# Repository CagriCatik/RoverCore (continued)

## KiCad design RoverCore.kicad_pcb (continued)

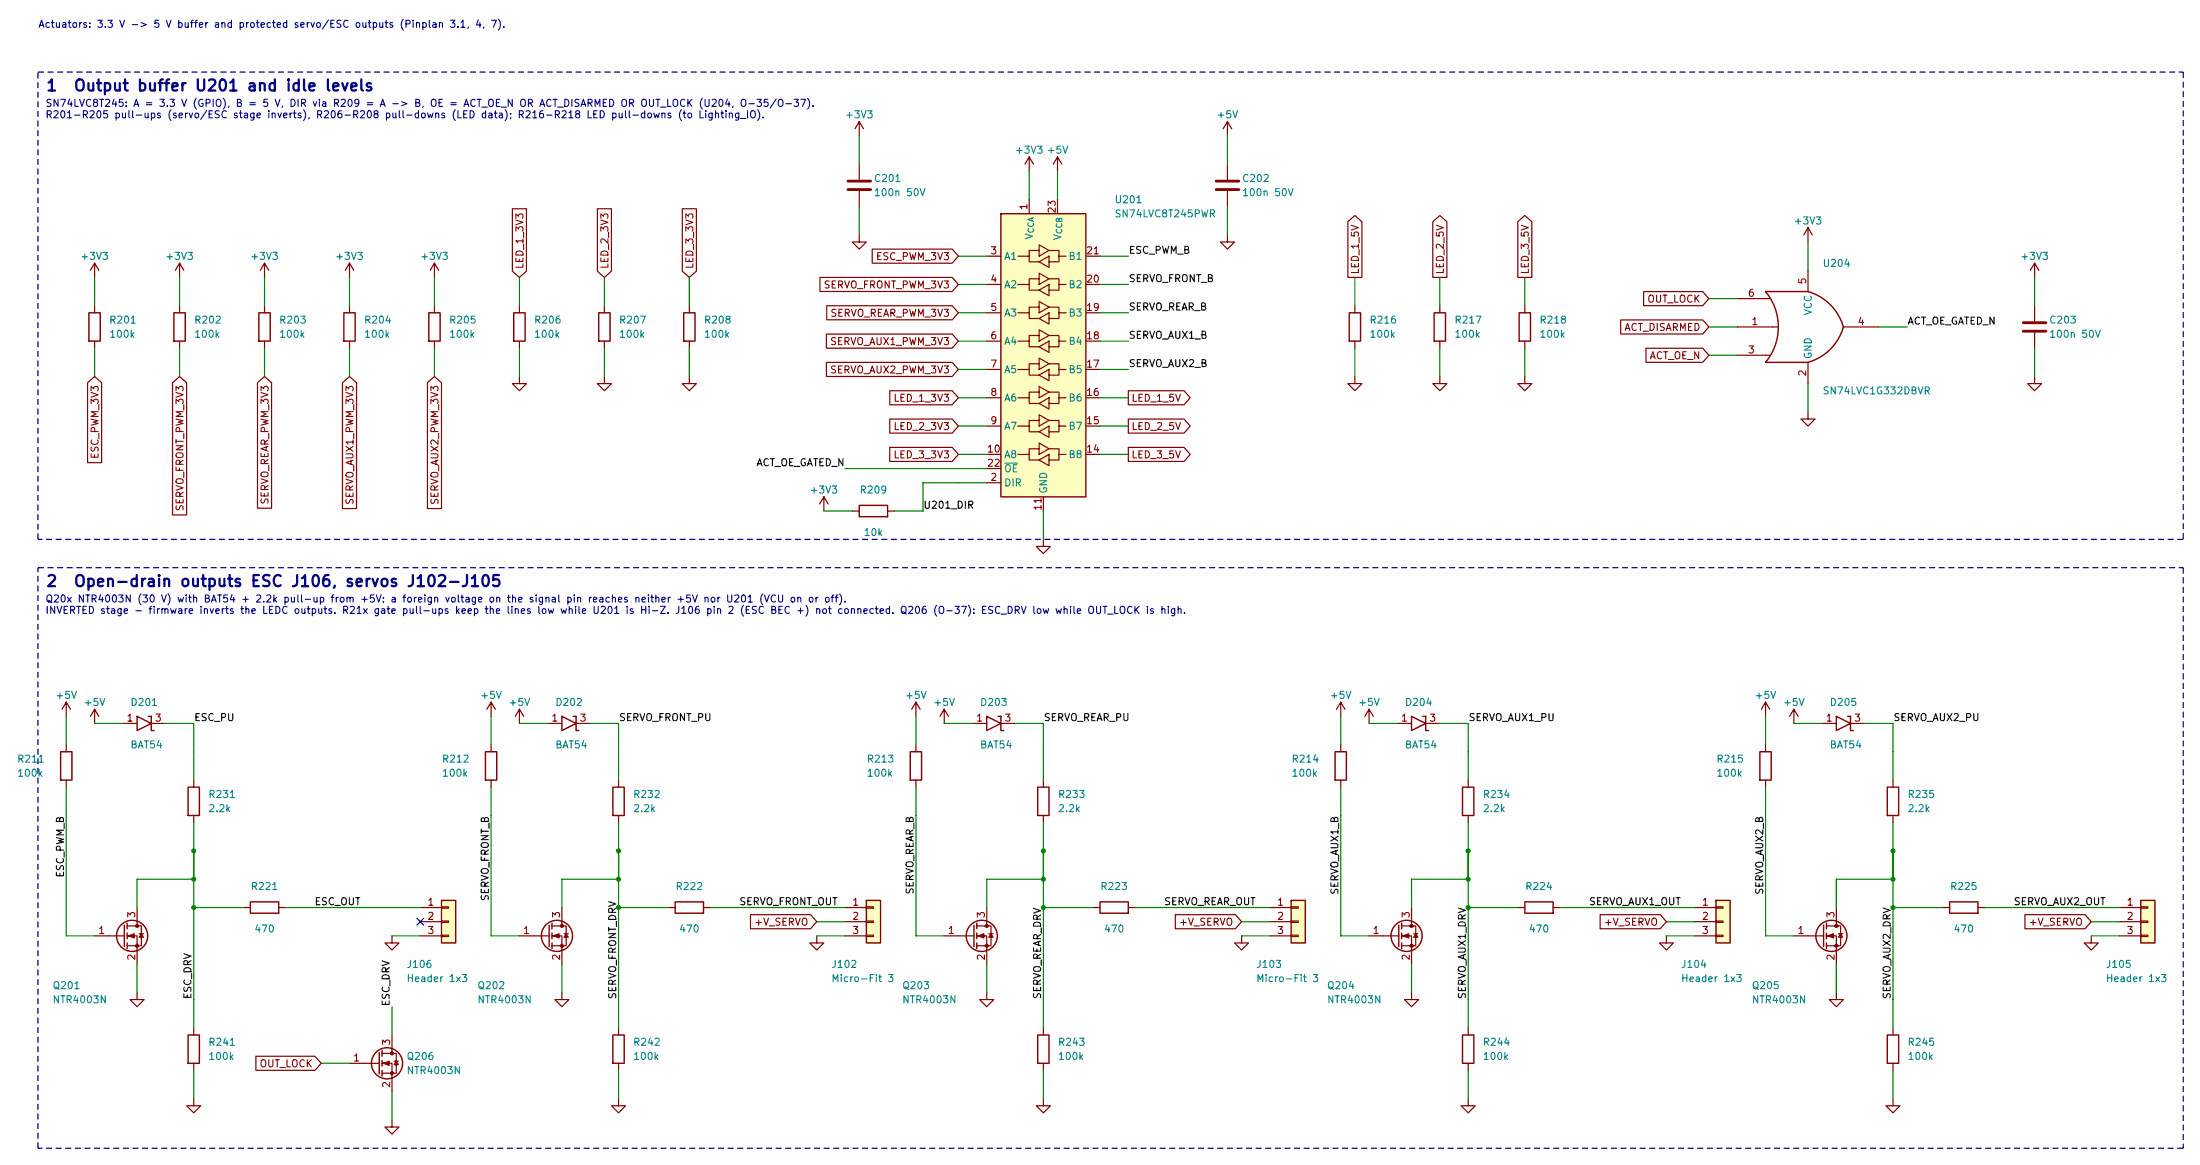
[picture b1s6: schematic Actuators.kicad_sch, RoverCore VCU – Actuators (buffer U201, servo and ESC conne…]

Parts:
C201, C202, C203: 100n 50V; C_0603_1608Metric; MPN CC0603KRX7R9BB104; LCSC C14663
D201, D202, D203, D204, D205: BAT54; SOT-23; MPN BAT54,215; LCSC C85084
J102, J103: Micro-Fit 3; Molex_Micro-Fit_3.0_43650-0300_1x03_P3.00mm_Horizontal; MPN 43650-0300; LCSC C503478
J104, J105, J106: Header 1x3; PinHeader_1x03_P2.54mm_Vertical; MPN 1x3 pin header 2.54 mm, vertical (part 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
Q201, Q202, Q203, Q204, Q205, Q206: NTR4003N; SOT-23; MPN NTR4003NT1G; LCSC C82325
R201, R202, R203, R204, R205, R206, R207, R208, R211, R212, R213, R214, R215, R216, R217, R218, R241, R242, R243, R244, R245: 100k; R_0603_1608Metric; MPN RC0603FR-07100KL; LCSC C14675
R209: 10k; R_0603_1608Metric; MPN RC0603FR-0710KL; LCSC C98220
R221, R222, R223, R224, R225: 470; R_0603_1608Metric; MPN RC0603FR-07470RL; LCSC C114669
R231, R232, R233, R234, R235: 2.2k; R_0603_1608Metric; MPN RC0603FR-072K2L; LCSC C114662
U201: SN74LVC8T245PWR; TSSOP-24_4.4x7.8mm_P0.65mm; MPN SN74LVC8T245PWR; LCSC C27643
U204: SN74LVC1G332DBVR; SOT-23-6; MPN SN74LVC1G332DBVR; LCSC C43368

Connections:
+3V3: C201.1, C203.1, R201.1, R202.1, R203.1, R204.1, R205.1, R209.1, U201.1 (V_{CCA}), U204.5 (VCC); also elsewhere on the board
+5V: C202.1, D201.1 (A), D202.1 (A), D203.1 (A), D204.1 (A), D205.1 (A), R211.1, R212.1, R213.1, R214.1, R215.1, U201.23 (V_{CCB}), U201.24 (V_{CCB}); also elsewhere on the board
+V_SERVO: J102.2, J103.2, J104.2, J105.2; also elsewhere on the board
/Actuators/ACT_OE_GATED_N: U201.22 (~OE), U204.4
/Actuators/ESC_DRV: Q201.3 (D), Q206.3 (D), R221.1, R231.2, R241.1
/Actuators/ESC_OUT: J106.1, R221.2
/Actuators/ESC_PU: D201.3 (K), R231.1
/Actuators/ESC_PWM_B: Q201.1 (G), R211.2, U201.21 (B1)
/Actuators/SERVO_AUX1_B: Q204.1 (G), R214.2, U201.18 (B4)
/Actuators/SERVO_AUX1_DRV: Q204.3 (D), R224.1, R234.2, R244.1
/Actuators/SERVO_AUX1_OUT: J104.1, R224.2
/Actuators/SERVO_AUX1_PU: D204.3 (K), R234.1
/Actuators/SERVO_AUX2_B: Q205.1 (G), R215.2, U201.17 (B5)
/Actuators/SERVO_AUX2_DRV: Q205.3 (D), R225.1, R235.2, R245.1
/Actuators/SERVO_AUX2_OUT: J105.1, R225.2
/Actuators/SERVO_AUX2_PU: D205.3 (K), R235.1
/Actuators/SERVO_FRONT_B: Q202.1 (G), R212.2, U201.20 (B2)
/Actuators/SERVO_FRONT_DRV: Q202.3 (D), R222.1, R232.2, R242.1
/Actuators/SERVO_FRONT_OUT: J102.1, R222.2
/Actuators/SERVO_FRONT_PU: D202.3 (K), R232.1
/Actuators/SERVO_REAR_B: Q203.1 (G), R213.2, U201.19 (B3)
/Actuators/SERVO_REAR_DRV: Q203.3 (D), R223.1, R233.2, R243.1
/Actuators/SERVO_REAR_OUT: J103.1, R223.2
/Actuators/SERVO_REAR_PU: D203.3 (K), R233.1
/Actuators/U201_DIR: R209.2, U201.2 (DIR)
ACT_DISARMED: U204.1; also elsewhere on the board
ACT_OE_N: U204.3; also elsewhere on the board
ESC_PWM_3V3: R201.2, U201.3 (A1); also elsewhere on the board
GND: C201.2, C202.2, C203.2, J102.3, J103.3, J104.3, J105.3, J106.3, Q201.2 (S), Q202.2 (S), Q203.2 (S), Q204.2 (S), Q205.2 (S), Q206.2 (S), R206.2, R207.2, R208.2, R216.2, R217.2, R218.2, R241.2, R242.2, R243.2, R244.2, R245.2, U201.11 (GND), U201.12 (GND), U201.13 (GND), U204.2 (GND); also elsewhere on the board
LED_1_3V3: R206.1, U201.8 (A6); also elsewhere on the board
LED_1_5V: R216.1, U201.16 (B6); also elsewhere on the board
LED_2_3V3: R207.1, U201.9 (A7); also elsewhere on the board
LED_2_5V: R217.1, U201.15 (B7); also elsewhere on the board
LED_3_3V3: R208.1, U201.10 (A8); also elsewhere on the board
LED_3_5V: R218.1, U201.14 (B8); also elsewhere on the board
OUT_LOCK: Q206.1 (G), U204.6; also elsewhere on the board
SERVO_AUX1_PWM_3V3: R204.2, U201.6 (A4); also elsewhere on the board
SERVO_AUX2_PWM_3V3: R205.2, U201.7 (A5); also elsewhere on the board
SERVO_FRONT_PWM_3V3: R202.2, U201.4 (A2); also elsewhere on the board
SERVO_REAR_PWM_3V3: R203.2, U201.5 (A3); also elsewhere on the board

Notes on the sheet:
1 Output buffer U201 and idle levels
SN74LVC8T245: A = 3.3 V (GPIO), B = 5 V, DIR via R209 = A -> B, OE = ACT_OE_N OR ACT_DISARMED OR OUT_LOCK (U204, O-35/O-37). R201-R205 pull-ups (servo/ESC stage inverts), R206-R208 pull-downs (LED data); R216-R218 LED pull-downs (to Lighting_IO).
2 Open-drain outputs ESC J106, servos J102-J105
Q20x NTR4003N (30 V) with BAT54 + 2.2k pull-up from +5V: a foreign voltage on the signal pin reaches neither +5V nor U201 (VCU on or off). INVERTED stage - firmware inverts the LEDC outputs. R21x gate pull-ups keep the lines low while U201 is Hi-Z. J106 pin 2 (ESC BEC +) not connected. Q206 (O-37):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
Actuators: 3.3 V -> 5 V buffer and protected servo/ESC outputs (Pinplan 3.1, 4, 7).

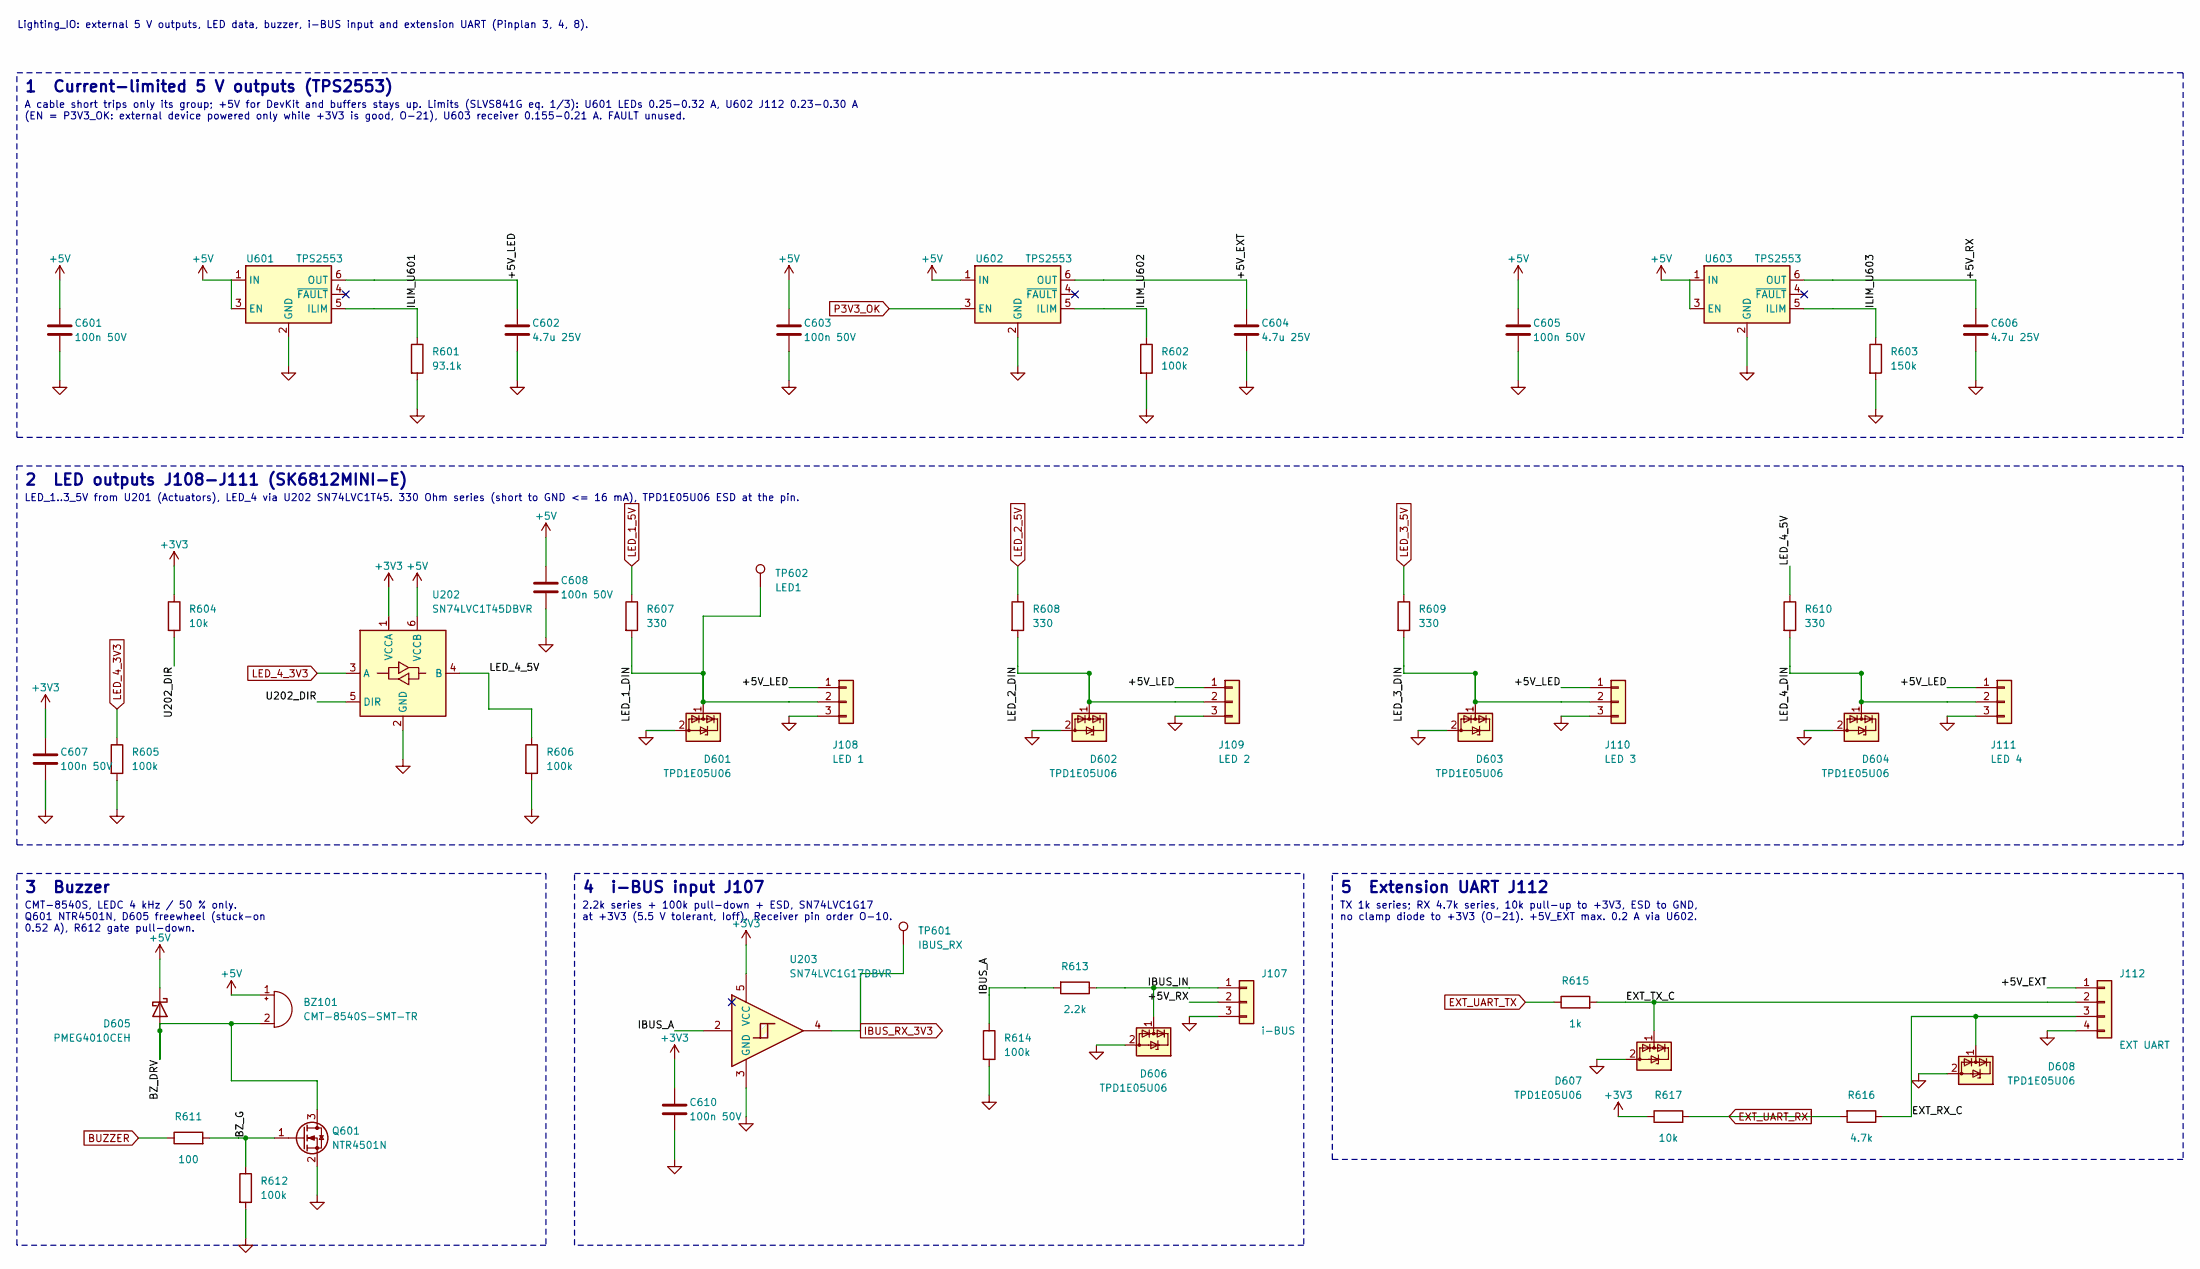
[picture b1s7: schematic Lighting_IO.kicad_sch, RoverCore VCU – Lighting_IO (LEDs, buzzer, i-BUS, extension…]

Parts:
BZ101: CMT-8540S-SMT-TR; MagneticBuzzer_SameSky_CMT-8540S-SMT; MPN CMT-8540S-SMT-TR; LCSC open (LCSC stock 0, O-23)
C601, C603, C605, C607, C608, C610: 100n 50V; C_0603_1608Metric; MPN CC0603KRX7R9BB104; LCSC C14663
C602, C604, C606: 4.7u 25V; C_0805_2012Metric; MPN CC0805KKX7R8BB475; LCSC C354262
D601, D602, D603, D604, D606, D607, D608: TPD1E05U06; Texas_DPY0002A_0.6x1mm_P0.65mm; MPN TPD1E05U06DPYR; LCSC C436349
D605: PMEG4010CEH; D_SOD-123F; MPN PMEG4010CEH,115; LCSC C193342
J107: i-BUS; PinHeader_1x03_P2.54mm_Vertical; MPN 1x3 pin header 2.54 mm (part open)
J108: LED 1; JST_PH_B3B-PH-K_1x03_P2.00mm_Vertical; MPN B3B-PH-K-S(LF)(SN); LCSC open (O-22)
J109: LED 2; JST_PH_B3B-PH-K_1x03_P2.00mm_Vertical; MPN B3B-PH-K-S(LF)(SN); LCSC open (O-22)
J110: LED 3; JST_PH_B3B-PH-K_1x03_P2.00mm_Vertical; MPN B3B-PH-K-S(LF)(SN); LCSC open (O-22)
J111: LED 4; JST_PH_B3B-PH-K_1x03_P2.00mm_Vertical; MPN B3B-PH-K-S(LF)(SN); LCSC open (O-22)
J112: EXT UART; JST_PH_B4B-PH-K_1x04_P2.00mm_Vertical; MPN B4B-PH-K-S(LF)(SN); LCSC open (O-22)
Q601: NTR4501N; SOT-23; MPN NTR4501NT1G; LCSC C85416
R601: 93.1k; R_0603_1608Metric; MPN RC0603FR-0793K1L; LCSC C273780
R602, R605, R606, R612, R614: 100k; R_0603_1608Metric; MPN RC0603FR-07100KL; LCSC C14675
R603: 150k; R_0603_1608Metric; MPN RC0603FR-07150KL; LCSC C114660
R604, R617: 10k; R_0603_1608Metric; MPN RC0603FR-0710KL; LCSC C98220
R607, R608, R609, R610: 330; R_0603_1608Metric; MPN RC0603FR-07330RL; LCSC C105881
R611: 100; R_0603_1608Metric; MPN RC0603FR-07100RL; LCSC C105588
R613: 2.2k; R_0603_1608Metric; MPN RC0603FR-072K2L; LCSC C114662
R615: 1k; R_0603_1608Metric; MPN RC0603FR-071KL; LCSC C22548
R616: 4.7k; R_0603_1608Metric; MPN RC0603FR-074K7L; LCSC C99782
TP601: IBUS_RX; TestPoint_Pad_D1.5mm
TP602: LED1; TestPoint_Pad_D1.5mm
U202: SN74LVC1T45DBVR; SOT-23-6; MPN SN74LVC1T45DBVR; LCSC C7843
U203: SN74LVC1G17DBVR; SOT-23-5; MPN SN74LVC1G17DBVR; LCSC C7836
U601, U602, U603: TPS2553; SOT-23-6; MPN TPS2553DBVR; LCSC C55266

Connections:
+3V3: C607.1, C610.1, R604.1, R617.1, U202.1 (VCCA), U203.5 (VCC); also elsewhere on the board
+5V: BZ101.1 (+), C601.1, C603.1, C605.1, C608.1, D605.1 (K), U202.6 (VCCB), U601.1 (IN), U601.3 (EN), U602.1 (IN), U603.1 (IN), U603.3 (EN); also elsewhere on the board
/Lighting_IO/+5V_EXT: C604.1, J112.1, U602.6 (OUT)
/Lighting_IO/+5V_LED: C602.1, J108.1, J109.1, J110.1, J111.1, U601.6 (OUT)
/Lighting_IO/+5V_RX: C606.1, J107.2, U603.6 (OUT)
/Lighting_IO/BZ_DRV: BZ101.2 (-), D605.2 (A), Q601.3 (D)
/Lighting_IO/BZ_G: Q601.1 (G), R611.2, R612.1
/Lighting_IO/EXT_RX_C: D608.1 (I/O), J112.3, R616.1
/Lighting_IO/EXT_TX_C: D607.1 (I/O), J112.2, R615.2
/Lighting_IO/IBUS_A: R613.2, R614.1, U203.2
/Lighting_IO/IBUS_IN: D606.1 (I/O), J107.1, R613.1
/Lighting_IO/ILIM_U601: R601.1, U601.5 (ILIM)
/Lighting_IO/ILIM_U602: R602.1, U602.5 (ILIM)
/Lighting_IO/ILIM_U603: R603.1, U603.5 (ILIM)
/Lighting_IO/LED_1_DIN: D601.1 (I/O), J108.2, R607.2, TP602.1
/Lighting_IO/LED_2_DIN: D602.1 (I/O), J109.2, R608.2
/Lighting_IO/LED_3_DIN: D603.1 (I/O), J110.2, R609.2
/Lighting_IO/LED_4_5V: R606.1, R610.1, U202.4 (B)
/Lighting_IO/LED_4_DIN: D604.1 (I/O), J111.2, R610.2
/Lighting_IO/U202_DIR: R604.2, U202.5 (DIR)
BUZZER: R611.1; also elsewhere on the board
EXT_UART_RX: R616.2, R617.2; also elsewhere on the board
EXT_UART_TX: R615.1; also elsewhere on the board
GND: C601.2, C602.2, C603.2, C604.2, C605.2, C606.2, C607.2, C608.2, C610.2, D601.2 (GND), D602.2 (GND), D603.2 (GND), D604.2 (GND), D606.2 (GND), D607.2 (GND), D608.2 (GND), J107.3, J108.3, J109.3, J110.3, J111.3, J112.4, Q601.2 (S), R601.2, R602.2, R603.2, R605.2, R606.2, R612.2, R614.2, U202.2 (GND), U203.3 (GND), U601.2 (GND), U602.2 (GND), U603.2 (GND); also elsewhere on the board
IBUS_RX_3V3: TP601.1, U203.4; also elsewhere on the board
LED_1_5V: R607.1; also elsewhere on the board
LED_2_5V: R608.1; also elsewhere on the board
LED_3_5V: R609.1; also elsewhere on the board
LED_4_3V3: R605.1, U202.3 (A); also elsewhere on the board
P3V3_OK: U602.3 (EN); also elsewhere on the board

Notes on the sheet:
1 Current-limited 5 V outputs (TPS2553)
A cable short trips only its group; +5V for DevKit and buffers stays up. Limits (SLVS841G eq. 1/3): U601 LEDs 0.25-0.32 A, U602 J112 0.23-0.30 A (EN = P3V3_OK: external device powered only while +3V3 is good, O-21), U603 receiver 0.155-0.21 A. FAULT unused.
2 LED outputs J108-J111 (SK6812MINI-E)
LED_1..3_5V from U201 (Actuators), LED_4 via U202 SN74LVC1T45. 330 Ohm series (short to GND <= 16 mA), TPD1E05U06 ESD at the pin.
3 Buzzer
CMT-8540S, LEDC 4 kHz / 50 % only. Q601 NTR4501N, D605 freewheel (stuck-on 0.52 A), R612 gate pull-down.
4 i-BUS input J107
2.2k series + 100k pull-down + ESD, SN74LVC1G17 at +3V3 (5.5 V tolerant, Ioff). Receiver pin order O-10.
5 Extension UART J112
TX 1k series; RX 4.7k series, 10k pull-up to +3V3, ESD to GND, no clamp diode to +3V3 (O-21). +5V_EXT max. 0.2 A via U602.
Lighting_IO: external 5 V outputs, LED data, buzzer, i-BUS input and extension UART (Pinplan 3, 4, 8).

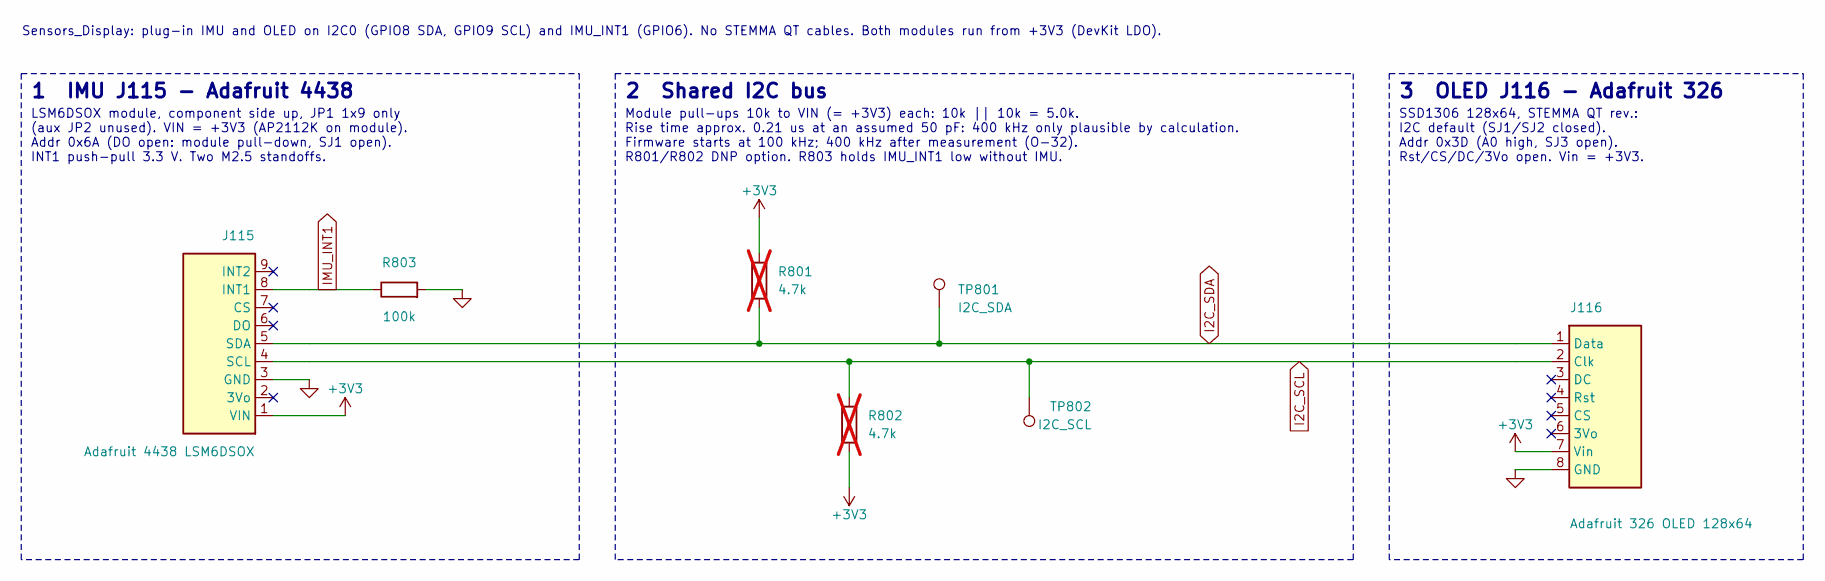
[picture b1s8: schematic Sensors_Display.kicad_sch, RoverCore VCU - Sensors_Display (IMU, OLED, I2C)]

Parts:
J115: Adafruit 4438 LSM6DSOX; Adafruit_4438_LSM6DSOX_Socket_1x09_P2.54mm; MPN SSW-109-01-T-S
J116: Adafruit 326 OLED 128x64; Adafruit_326_OLED128x64_Socket_1x08_P2.54mm; MPN SSW-108-01-T-S
R801, R802: 4.7k; R_0603_1608Metric; MPN RC0603FR-074K7L; not fitted
R803: 100k; R_0603_1608Metric; MPN RC0603FR-07100KL; LCSC C14675
TP801: I2C_SDA; TestPoint_Pad_D1.5mm
TP802: I2C_SCL; TestPoint_Pad_D1.5mm

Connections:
+3V3: J115.1 (VIN), J116.7 (Vin), R801.1, R802.2; also elsewhere on the board
GND: J115.3 (GND), J116.8 (GND), R803.2; also elsewhere on the board
I2C_SCL: J115.4 (SCL), J116.2 (Clk), R802.1, TP802.1; also elsewhere on the board
I2C_SDA: J115.5 (SDA), J116.1 (Data), R801.2, TP801.1; also elsewhere on the board
IMU_INT1: J115.8 (INT1), R803.1; also elsewhere on the board

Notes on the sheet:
1 IMU J115 - Adafruit 4438
LSM6DSOX module, component side up, JP1 1x9 only (aux JP2 unused). VIN = +3V3 (AP2112K on module). Addr 0x6A (DO open: module pull-down, SJ1 open). INT1 push-pull 3.3 V. Two M2.5 standoffs.
2 Shared I2C bus
Module pull-ups 10k to VIN (= +3V3) each: 10k || 10k = 5.0k. Rise time approx. 0.21 us at an assumed 50 pF: 400 kHz only plausible by calculation. Firmware starts at 100 kHz; 400 kHz after measurement (O-32). R801/R802 DNP option. R803 holds IMU_INT1 low without IMU.
3 OLED J116 - Adafruit 326
SSD1306 128x64, STEMMA QT rev.: I2C default (SJ1/SJ2 closed). Addr 0x3D (A0 high, SJ3 open). Rst/CS/DC/3Vo open. Vin = +3V3.
Sensors_Display: plug-in IMU and OLED on I2C0 (GPIO8 SDA, GPIO9 SCL) and IMU_INT1 (GPIO6). No STEMMA QT cables. Both modules run from +3V3 (DevKit LDO).

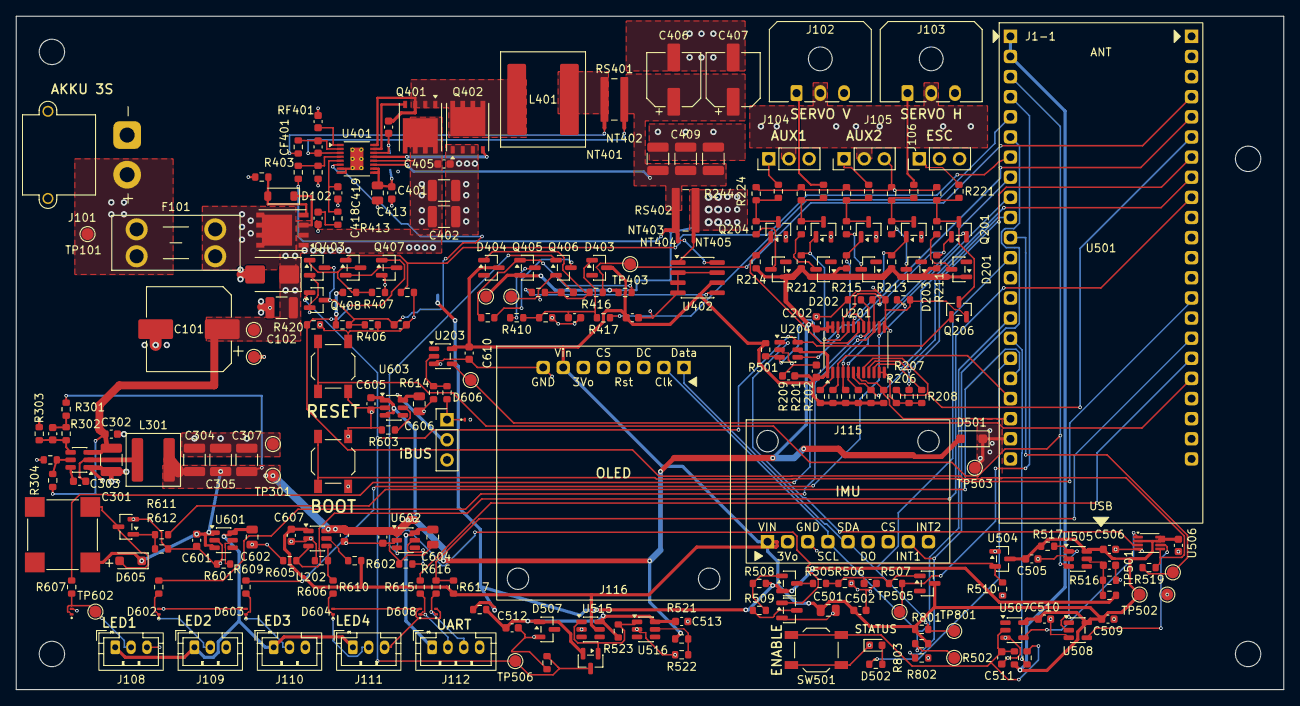
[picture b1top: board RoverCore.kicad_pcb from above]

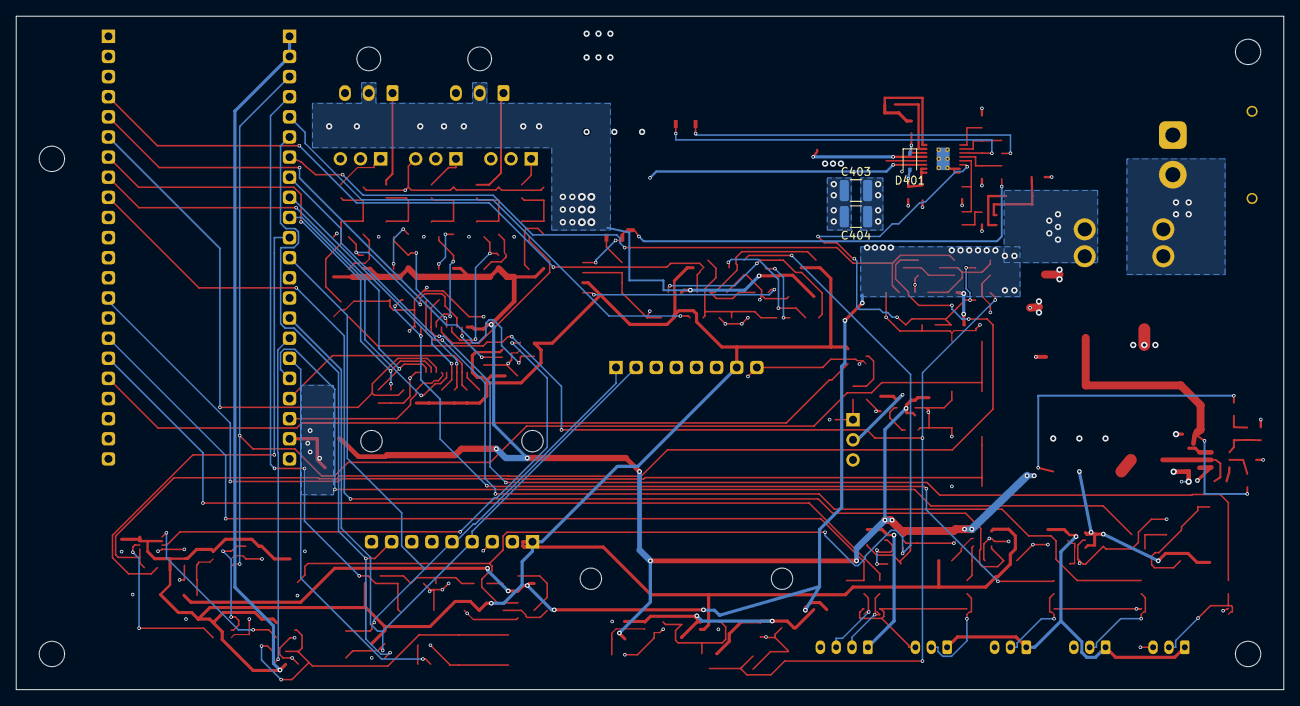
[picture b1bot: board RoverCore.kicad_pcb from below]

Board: 4 copper layers, 160.0 x 85.0 mm, 257 parts (3 on the bottom side), 126 nets.

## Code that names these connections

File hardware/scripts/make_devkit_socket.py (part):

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NAME = "ESP32-S3-DevKitC-1_Socket"
FP_NAME = "ESP32-S3-DevKitC-1_v1.1_Socket_2x1x22_P2.54mm"

J1 = ["3V3", "3V3", "RST", "GPIO4", "GPIO5", "GPIO6", "GPIO7", "GPIO15", "GPIO16", "GPIO17", "GPIO18",
      "GPIO8", "GPIO3", "GPIO46", "GPIO9", "GPIO10", "GPIO11", "GPIO12", "GPIO13", "GPIO14", "5V", "G"]
J3 = ["G", "TX", "RX", "GPIO1", "GPIO2", "GPIO42", "GPIO41", "GPIO40", "GPIO39", "GPIO38", "GPIO37",
      "GPIO36", "GPIO35", "GPIO0", "GPIO45", "GPIO48", "GPIO47", "GPIO21", "GPIO20", "GPIO19", "G", "G"]
assert len(J1) == len(J3) == 22

PITCH, ROW = 2.54, 22.86
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
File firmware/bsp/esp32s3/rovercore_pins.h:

/* GENERATED by firmware/tools/gen_pins.py from hardware/interfaces/pinmap.csv - do not edit. */
#ifndef ROVERCORE_PINS_H
#define ROVERCORE_PINS_H

#define PIN_ISERVO_SENSE      1  /* ISERVO_SENSE         in-analog pinmap: draft */
#define PIN_ACT_OE_N          2  /* ACT_OE_N             out       pinmap: draft */
#define PIN_VBAT_SENSE        4  /* VBAT_SENSE           in-analog pinmap: draft */
#define PIN_VSERVO_SENSE      5  /* VSERVO_SENSE         in-analog pinmap: draft */
#define PIN_IMU_INT1          6  /* IMU_INT1             in        pinmap: draft */
#define PIN_SERVO_PWR_EN      7  /* SERVO_PWR_EN         out       pinmap: draft */
#define PIN_I2C_SDA           8  /* I2C_SDA              bidir     pinmap: draft */
#define PIN_I2C_SCL           9  /* I2C_SCL              out       pinmap: draft */
#define PIN_ENABLE_BTN       10  /* ENABLE_BTN_N         in        pinmap: draft */
#define PIN_STATUS_LED       11  /* STATUS_LED           out       pinmap: draft */
#define PIN_BUZZER           12  /* BUZZER               out       pinmap: draft */
#define PIN_ESC              13  /* ESC_PWM_3V3          out       pinmap: draft */
#define PIN_SERVO_AUX2       14  /* SERVO_AUX2_PWM_3V3   out       pinmap: draft */
#define PIN_SERVO_FRONT      15  /* SERVO_FRONT_PWM_3V3  out       pinmap: draft */
#define PIN_SERVO_REAR       16  /* SERVO_REAR_PWM_3V3   out       pinmap: draft */
#define PIN_SERVO_AUX1       17  /* SERVO_AUX1_PWM_3V3   out       pinmap: draft */
#define PIN_ACT_ARMED_FB     18  /* ACT_ARMED_FB         in        pinmap: draft */
#define PIN_IBUS_RX          21  /* IBUS_RX_3V3          in        pinmap: draft */
#define PIN_LED_4            39  /* LED_4_3V3            out       pinmap: draft */
#define PIN_LED_3            40  /* LED_3_3V3            out       pinmap: draft */
#define PIN_LED_2            41  /* LED_2_3V3            out       pinmap: draft */
#define PIN_LED_1            42  /* LED_1_3V3            out       pinmap: draft */
#define PIN_EXT_TX           47  /* EXT_UART_TX          out       pinmap: draft */
#define PIN_EXT_RX           48  /* EXT_UART_RX          in        pinmap: draft */

#define ROVERCORE_PIN_COUNT 24

#endif

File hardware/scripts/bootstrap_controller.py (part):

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- 3.3 V: the DevKit LDO is the only 3.3 V source (+3V3); carrier load <= 50 mA.
- Fail-safe: ACT_OE_N pulled up (buffers off); the servo rail default OFF lives on ServoPower
  (SERVO_PWR_EN, R414/R407/Q404/R415) so it holds without this sheet's parts.
Signals to the other sheets are global labels; VBAT_PROT comes hierarchically from Power.

Usage: python3 hardware/scripts/bootstrap_controller.py
"""
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# DevKit socket pin -> net (pads 1-22 = J1-1..22, 23-44 = J3-1..22); "NC" = reserved, see pinmap.csv
SOCKET = {
    1: "+3V3", 2: "=1", 3: "NC", 4: "VBAT_SENSE", 5: "VSERVO_SENSE", 6: "IMU_INT1", 7: "SERVO_PWR_EN",
    8: "SERVO_FRONT_PWM_3V3", 9: "SERVO_REAR_PWM_3V3", 10: "SERVO_AUX1_PWM_3V3", 11: "SPARE_GPIO18",
    12: "I2C_SDA", 13: "NC", 14: "NC", 15: "I2C_SCL", 16: "ENABLE_BTN_N", 17: "STATUS_LED", 18: "BUZZER",
    19: "ESC_PWM_3V3", 20: "SERVO_AUX2_PWM_3V3", 21: "+5V_DEVKIT", 22: "GND",
    23: "GND", 24: "NC", 25: "NC", 26: "ISERVO_SENSE", 27: "ACT_OE_N", 28: "LED_1_3V3", 29: "LED_2_3V3",
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        ("D506", "ProjectSymbols:BAT54_SOT23", "BAT54", "Package_TO_SOT_SMD:SOT-23", (345.44, 124.46, 90),
         {"1": "VBAT_DIV", "3": "+3V3"}, dict(DBAT54)),
        ("R507", "Device:R", "10k", R0603, (360.68, 144.78, 0), {"1": "VBAT_DIV", "2": "VBAT_SENSE"},
         rc("RC0603FR-0710KL", "C98220", "Series resistor to GPIO4 (the voltage bound is D506)")),
        ("Q505", "Transistor_FET:Q_PMOS_GSD", "NTR4171P", "Package_TO_SOT_SMD:SOT-23", (297.18, 50.8, 0),
         {"1": "VBAT_SW_G", "2": "VBAT_PROT", "3": "VBAT_SW"},
         dict(QNTR4171, Description="O-21: normally-off switch for the VBAT divider; on only while P3V3_OK is high. " + QNTR4171["Description"])),
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         rc("RC0603FR-07100KL", "C14675", "P3V3_OK pull-down: low while U504 is unpowered (VDD < 0.7 V) or the DevKit is missing")),
        ("TP505", "Connector:TestPoint", "VBAT_SENSE", TP, (345.44, 104.14, 0), {"1": "VBAT_SENSE"},
         {"_ref_at": (2.54, -1.27), "_val_at": (2.54, 1.27), "Description": "Test point VBAT_SENSE; bare copper pad, excluded from BOM"}),
        ("TP501", "Connector:TestPoint", "GPIO18", TP, (368.3, 104.14, 0), {"1": "SPARE_GPIO18"},
         {"_ref_at": (2.54, -1.27), "_val_at": (2.54, 1.27), "Description": "Spare GPIO18 (input only: high- and low-level power-up glitch); bare copper pad"}),
    ]


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    s.note("Defaults with ESP32 in reset, booting or missing: servo rail OFF (ServoPower R414/Q404/R415), "
           "output buffers Hi-Z (R501), buzzer off, button reads high. Firmware: rail first, then ACT_OE_N low.",
           25.4, 40.64, "h3")
    s.note("O-21: U504 (TLV809E) sets P3V3_OK only while +3V3 >= 2.93 V; it closes the divider switches Q505/Q405 and enables +5V_EXT. BAT54 clamps hold ADC pins <= VDD + 0.24 V.",
           25.4, 45.72, "h4")
    return s.render()

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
